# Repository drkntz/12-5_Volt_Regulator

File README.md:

# 12-5_Volt_Regulator
12 to 5 volt DC regulator @ 3A

#Schematic rev 2

#Layout rev 2

#3-D PCB Image rev 2

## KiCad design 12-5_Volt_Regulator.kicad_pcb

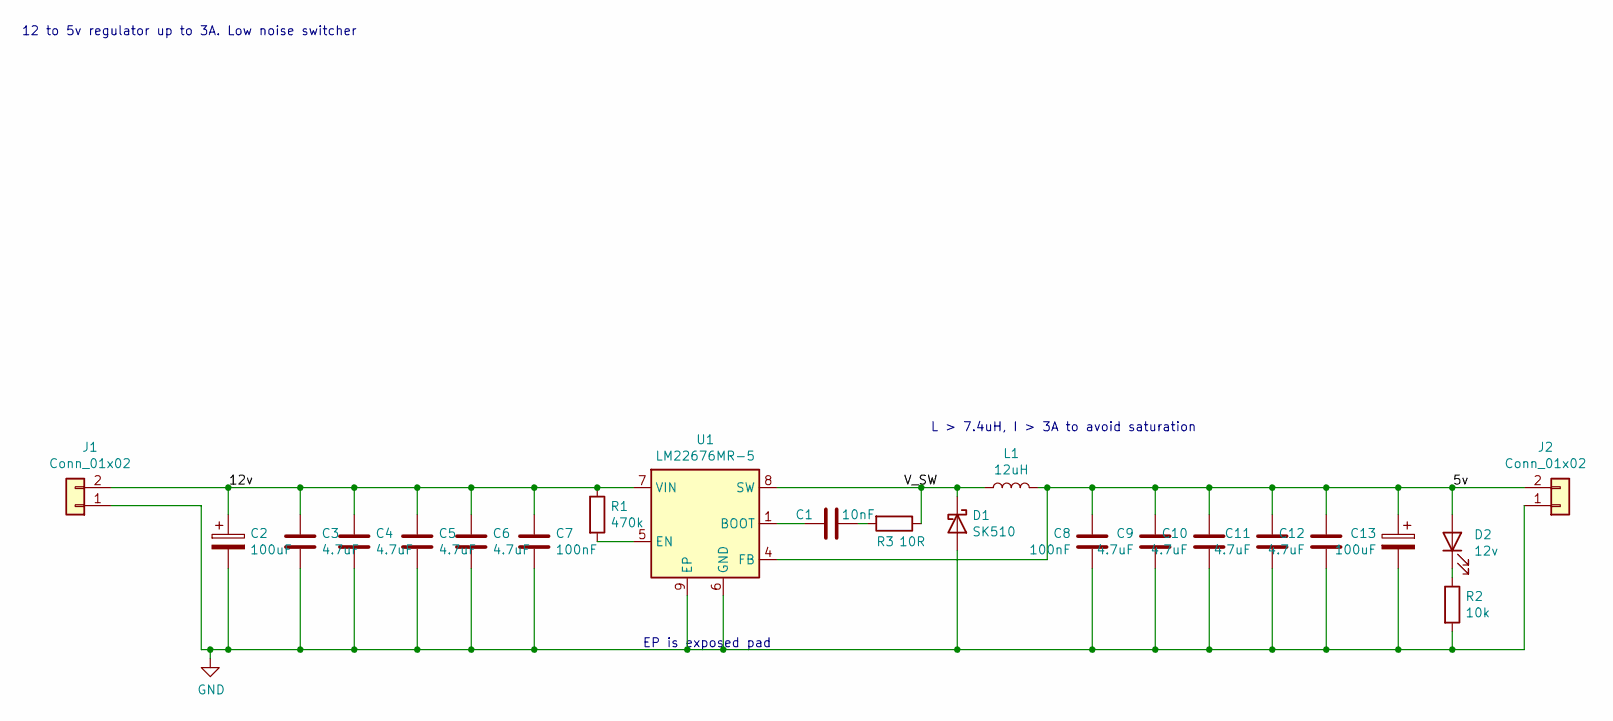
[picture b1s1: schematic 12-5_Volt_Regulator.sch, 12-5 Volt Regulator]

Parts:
C1: 10nF; C_0603_1608Metric
C2, C13: 100uF; CP_Elec_8x10.5
C3, C4, C5, C6, C9, C10, C11, C12: 4.7uF; C_1206_3216Metric
C7, C8: 100nF; C_0805_2012Metric
D1: SK510; D_SMC
D2: 12v; LED_D3.0mm
J1, J2: Conn_01x02; PinHeader_1x02_P2.54mm_Vertical
L1: 12uH; L_Bourns_SRP7028A_7.3x6.6mm
R1: 470k; R_0805_2012Metric
R2: 10k; R_0805_2012Metric
R3: 10R; R_0603_1608Metric
U1: LM22676MR-5; TI_SO-PowerPAD-8

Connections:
/5v: C8.1, C9.1, C10.1, C11.1, C12.1, C13.1, D2.2 (A), J2.2, L1.2, U1.4 (FB)
/12v: C2.1, C3.1, C4.1, C5.1, C6.1, C7.1, J1.2, R1.1, U1.7 (VIN)
/V_SW: D1.1 (K), L1.1, R3.1, U1.8 (SW)
GND: C2.2, C3.2, C4.2, C5.2, C6.2, C7.2, C8.2, C9.2, C10.2, C11.2, C12.2, C13.2, D1.2 (A), J1.1, J2.1, R2.2, U1.6 (GND), U1.9 (EP)
unnamed: C1.1, R3.2
unnamed: C1.2, U1.1 (BOOT)
unnamed: D2.1 (K), R2.1
unnamed: R1.2, U1.5 (EN)

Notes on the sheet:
12 to 5v regulator up to 3A. Low noise switcher
EP is exposed pad
L > 7.4uH, I > 3A to avoid saturation

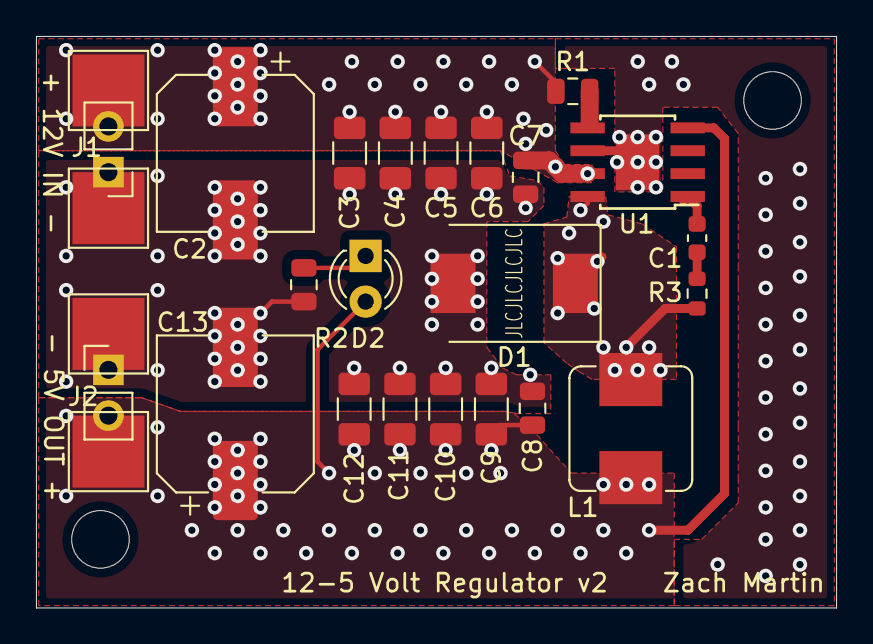
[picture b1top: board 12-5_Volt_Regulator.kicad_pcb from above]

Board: 2 copper layers, 44.4 x 31.8 mm, 22 parts (0 on the bottom side), 8 nets.

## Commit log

2021-07-20 Initial commit: TI simple switcher, v0 board layout
2021-07-20 Added wire pads, removed vias & fills as I switched grid spacing
2021-07-20 Re-routed zone boundaries
2021-07-20 Updated vias, traces, fills, JLCPCB part # location. Ready for ordering
2021-07-20 Gerbers
2021-07-21 cleanup
2022-02-01 Rev 2. Fixed feedback loop, added R3 for EMI suppression
